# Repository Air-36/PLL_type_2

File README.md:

# 🚀 Phase Locked loop 
This project is  done in order to understanding the working and designing of Phase locked Loops, that forms basics for most of electronic circuits.   

---

## 📸 Software Screenshots
- Schematics   

- 2 layer fill view of PCB   

- 3D view of PCB   

---
## 📸 Hardware Views
- Fabricated PCB   

- Final Product   

---

## 🎥 Working Video

>    

---

## ✨ Features

- Primary loop that fine tunes and locks freuency at specified frequency (doubles).
- Integrated frequency loop acts as coarse tuning and frequency stabilizing.
- Working range of input: 5kHz - 25kHz.
- 100% duty cycle of output.

---

## 🧰 Technologies/Softwares Used

- **LTSpice**
- **KiCAD**

---

## 👨‍💻 Teammates

| Name                                                  | Course                                          |
|-------------------------------------------------------|-------------------------------------------------|
| [Shrinivas B M](https://github.com/Air-36)            | B.tech, Electronics & Communication Engineering |
| [S. Sirichandana](https://github.com/sirichandana138) | B.tech, Electical Engineering                   |
| Darshini kinni                                        | B.tech, Mechanical Engineering                  |

## 👨‍🏫Supervision
This project was completed under the guidance of:

[Dr. Nijwm Wary](https://nijwmwary.com/)  
School of Electrical and computer sciences,  
Indian Institute of technology,    
Bhubaneshwar

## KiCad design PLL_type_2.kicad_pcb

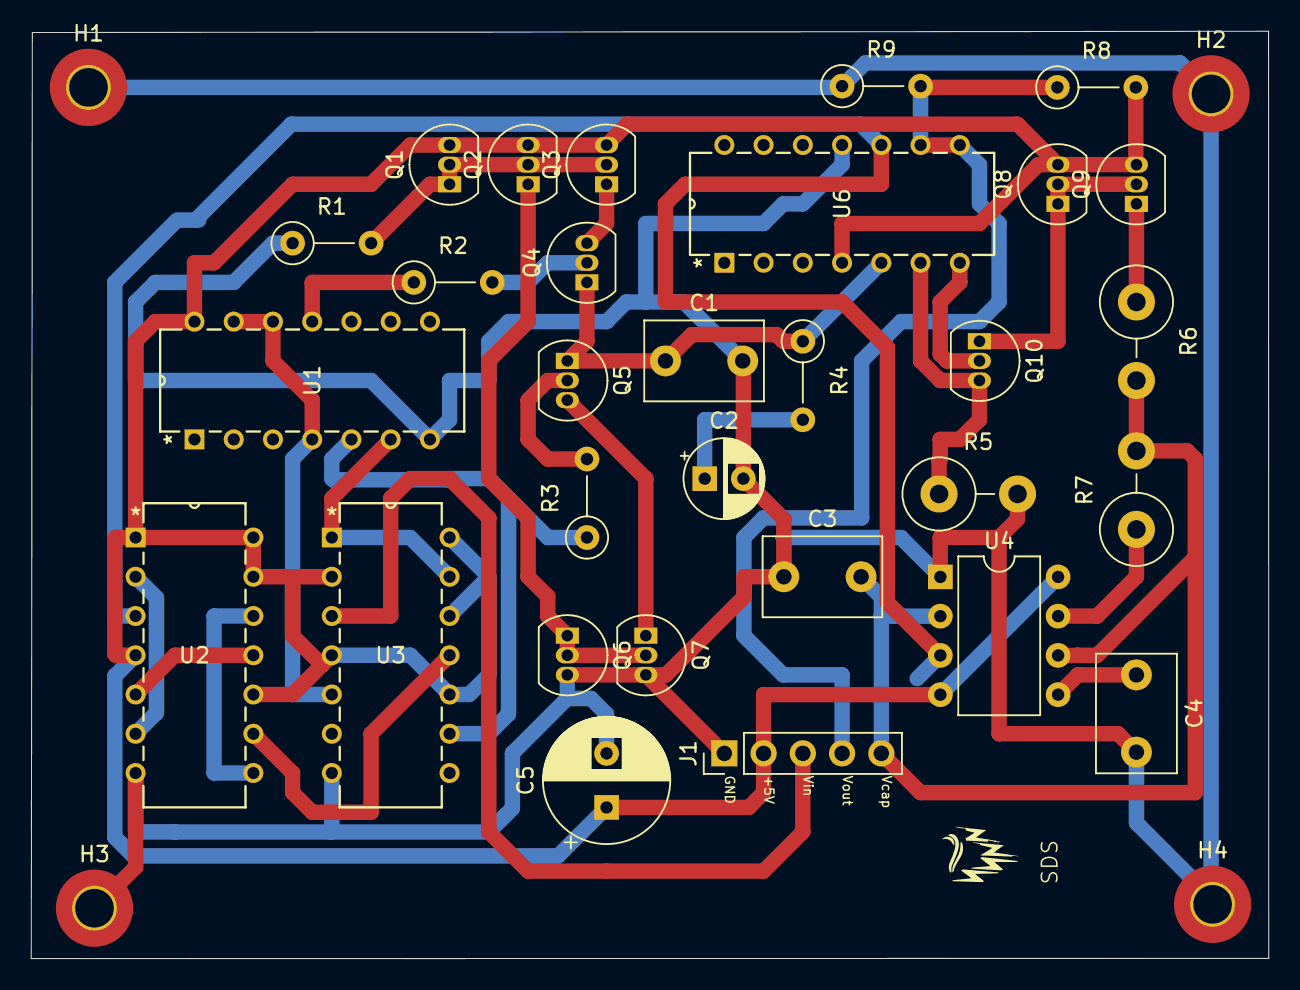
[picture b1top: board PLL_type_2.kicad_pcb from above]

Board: 2 copper layers, 80.1 x 60.0 mm, 35 parts (0 on the bottom side), 29 nets.

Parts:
,: .; Logo
C1, C3, C4: 10n; C_Disc_D7.5mm_W5.0mm_P5.00mm
C2: 100n; CP_Radial_D5.0mm_P2.50mm
C5: 220u; CP_Radial_D8.0mm_P3.50mm
H1, H2, H3, H4: MountingHole_Pad; MountingHole_2.5mm_Pad_TopBottom
J1: Conn_01x05_Pin; PinHeader_1x05_P2.54mm_Vertical
Q1, Q2, Q3, Q4, Q8, Q9: BC557; TO-92_Inline
Q5, Q6, Q7, Q10: BC547; TO-92_Inline
R1, R2, R3: 10k; R_Axial_DIN0207_L6.3mm_D2.5mm_P5.08mm_Vertical
R4: 5.1k; R_Axial_DIN0207_L6.3mm_D2.5mm_P5.08mm_Vertical
R5: 1k; R_Axial_DIN0414_L11.9mm_D4.5mm_P5.08mm_Vertical
R6, R7: 100; R_Axial_DIN0414_L11.9mm_D4.5mm_P5.08mm_Vertical
R8, R9: 5k; R_Axial_DIN0207_L6.3mm_D2.5mm_P5.08mm_Vertical
U1: CD74HCT00E; N14
U2, U3: CD74HCT74E; N14
U4: NA555P; DIP-8_W7.62mm
U6: LM324AN; N14

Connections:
GND: C1.2, C2.2, C3.1, C4.2, C5.2, H1.1, H2.1, H3.1, H4.1, J1.1, Q6.3 (E), Q7.3 (E), R1.1, R5.2, R9.1, U1.7 (GND), U2.7 (GND), U3.7 (GND), U4.1 (GND), U6.11 (GND)
unnamed: C2.1, R4.2
unnamed: Q1.1 (C), Q1.2 (B), Q2.2 (B), Q3.2 (B), R1.2
unnamed: Q2.1 (C), Q6.1 (C), Q6.2 (B), Q7.2 (B)
unnamed: Q3.1 (C), Q4.3 (E)
unnamed: Q4.2 (B), R2.2
unnamed: C1.1, Q4.1 (C), Q5.1 (C), R4.1, U6.5 (2IN+)
unnamed: Q5.2 (B), R3.2
unnamed: Q5.3 (E), Q7.1 (C)
unnamed: Q9.1 (C), R6.1
unnamed: Q10.2 (B), U6.7 (2OUT)
unnamed: Q8.1 (C), Q8.2 (B), Q9.2 (B), Q10.1 (C)
unnamed: Q10.3 (E), R5.1, U6.6 (2IN-)
unnamed: U1.4 (2A), U1.12 (4A), U1.13 (4B), U3.5 (1Q)
unnamed: R3.1, U1.5 (2B), U3.9 (2Q)
unnamed: U1.6 (2Y), U3.1 (*1R), U3.13 (*2R)
unnamed: R2.1, U1.11 (4Y)
unnamed: U2.3 (1CP), U4.3 (Q), U6.10 (3IN+)
unnamed: U2.5 (1Q), U2.11 (2CP)
unnamed: U2.9 (2Q), U3.11 (2CP)
unnamed: U2.2 (1D), U2.6 (*1Q)
unnamed: U2.8 (*2Q), U2.12 (2D)
unnamed: C4.1, U4.5 (CV)
unnamed: R7.1, U4.7 (DIS)
unnamed: R8.1, R9.2, U6.9 (3IN-)
VDD: C5.1, J1.2, Q1.3 (E), Q2.3 (E), Q3.3 (E), Q8.3 (E), Q9.3 (E), R8.2, U1.14 (VCC), U2.1 (*1R), U2.4 (*1S), U2.10 (*2S), U2.13 (*2R), U2.14 (VCC), U3.2 (1D), U3.4 (*1S), U3.10 (*2S), U3.12 (2D), U3.14 (VCC), U4.4 (R), U4.8 (VCC), U6.4 (VCC)
vcap: C3.2, J1.5, R6.2, R7.2, U4.2 (TR), U4.6 (THR)
vin: J1.3, U3.3 (1CP)
vout: J1.4, U6.8 (3OUT)

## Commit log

2025-07-06 tested and working
2025-07-06 Readme Update
